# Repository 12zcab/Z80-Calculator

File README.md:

BASED ON PREVIOUS PROJECT [View github Repo](https://github.com/12zcab/Handheld-Z80-Retro-Computer)
# What is this?
This is a portable handheld computer made with z80 customized for assembly language programming and simplified system for educational purpose.
The computer contains a Z80 cpu,a 1602 or 2004 LCD and 2 EEPROM slot,a RAM slot,a buzzer with IO ic driver
Its originally designed for another project and edited for better performance as a programmable calculator.
The circuit is edited to make it more simple.

# What it does?
It's a calculator that you can do programming on!
My final goal is to do complex trigonometry and statistic calculation on this calculator!
Also hopefully I can do a Bad Apple Animation on this device XD

Main Functions:
|Type|Function|
|-|-|
|Varaible|ABCDEHIJKLMNOPQRSTUVWXYZ 26 in total :D Hopefully can support 1*10^-99 to 9.999999999*10^99|
|basic operation|+ - * /|
|Trigo|Sin Cos Tan,ArcSin ArcCos ArcTan|
|Sqrt and indexes|^ NthRoot Sqr Sqrt|
|Log|Ln,Log,e^,10^|
|Formula|Save custom formula to input variables and output the result|
# Why it exists?
I just learnt how computer calculates complicated functions with taylor series simplification and I wanna try it in real life and make my own cool retro calculator :D

# Basic Structure

\##Memory Map

|Address|Compoenent|Function|
|-|-|-|
|0x0000 - 0x7FFF|EEPROM|Executable Code of Operating System|
|0x8000 - 0xFEFF|RAM or EEPROM|Multibanked External EEPROM and RAM|
|0xFF00 - 0xFFFF|IO Outputs|for LCD Buzzer and Keyboard Input Output|
|----|----|----|

# Compoenents
## Main Compoenents

|Name|Usage|Quantity|
|-|-|-|

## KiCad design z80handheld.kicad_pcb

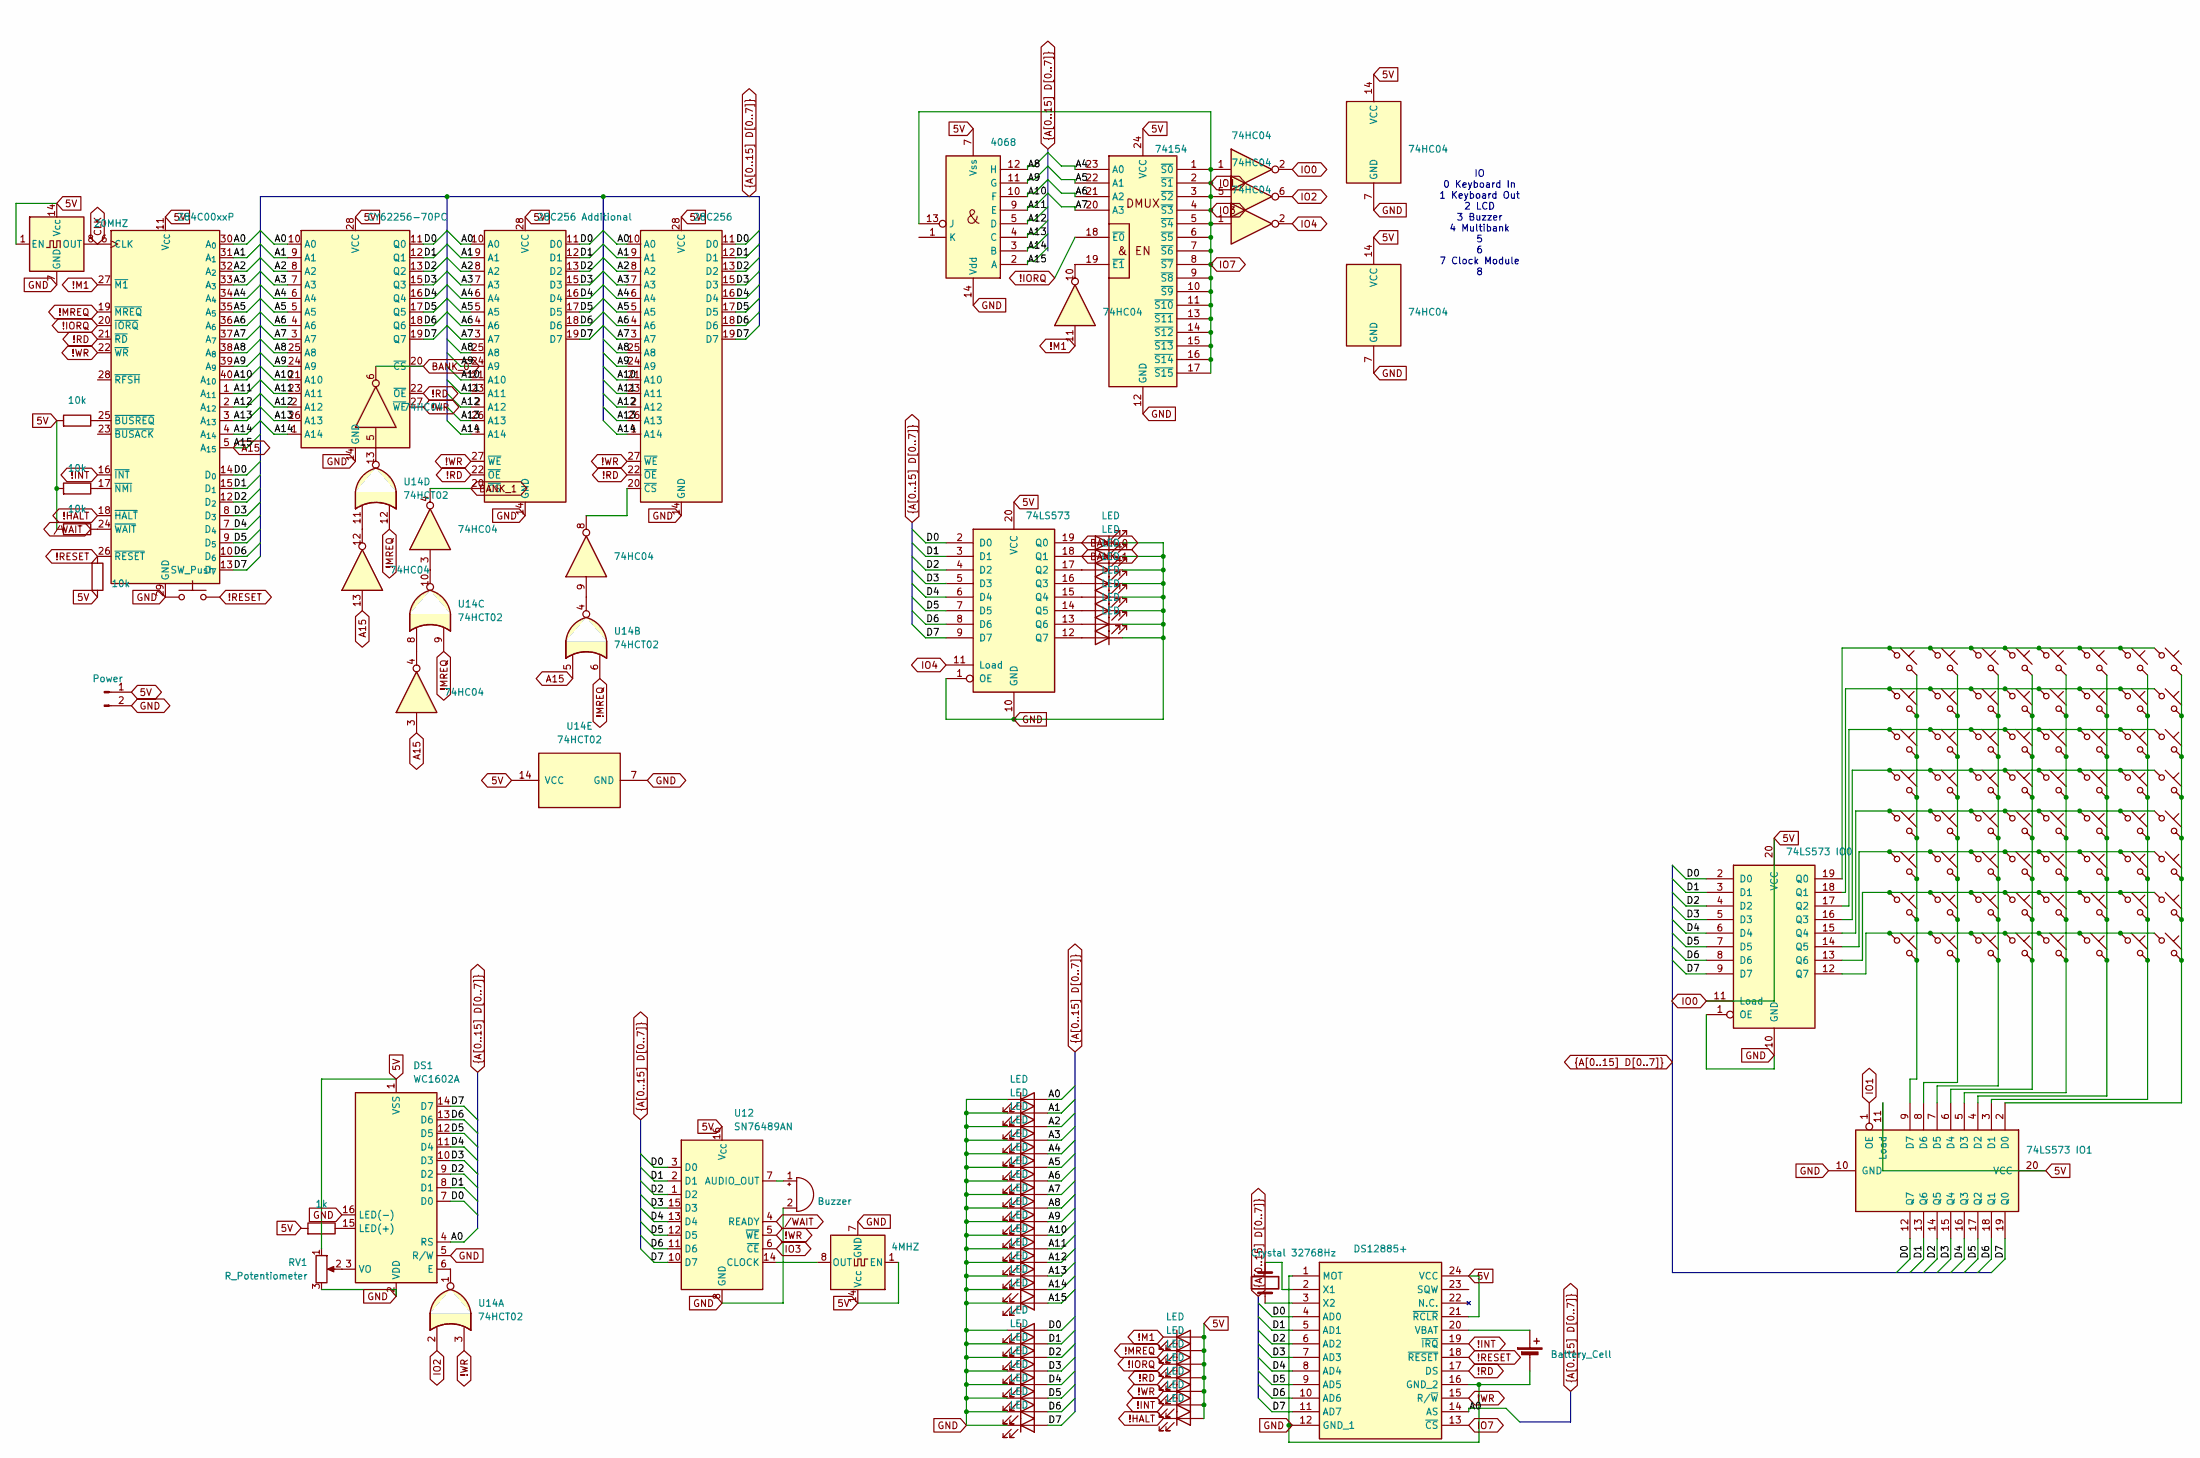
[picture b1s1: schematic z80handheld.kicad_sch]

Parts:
BT1: Battery_Cell; BatteryHolder_MYOUNG_BS-07-A1BJ001_CR2032
BZ1: Buzzer; Buzzer_12x9.5RM7.6
D1, D2, D3, D4, D5, D6, D7, D8, D9, D10, D11, D12, D13, D14, D15, D16, D17, D18, D19, D20, D21, D22, D23, D24, D25, D26, D27, D28, D29, D30, D31, D32, D33, D34, D35, D36, D37, D38, D39: LED; LED_D5.0mm
DS1: WC1602A
IC1: DS12885+; DIP1524W51P254L3175H508Q24N; Manufacturer_Part_Number DS12885+; Mouser Part Number 700-DS12885
J1: Power; PinHeader_1x02_P2.54mm_Vertical
R1, R2, R3, R5: 10k; R_Axial_DIN0207_L6.3mm_D2.5mm_P7.62mm_Horizontal
R4: 1k; R_Axial_DIN0207_L6.3mm_D2.5mm_P7.62mm_Horizontal
RV1: R_Potentiometer; Potentiometer_ACP_CA9-V10_Vertical
SW1, SW2, SW3, SW4, SW5, SW6, SW7, SW8, SW9, SW10, SW11, SW12, SW13, SW14, SW15, SW16, SW17, SW18, SW19, SW20, SW21, SW22, SW23, SW24, SW25, SW26, SW27, SW28, SW29, SW30, SW31, SW32, SW33, SW34, SW35, SW36, SW37, SW38, SW39, SW40, SW41, SW42, SW43, SW44, SW45, SW46, SW47, SW48, SW49, SW50, SW51, SW52, SW53, SW54, SW55, SW56, SW57, SW58, SW59, SW60, SW61, SW62, SW63, SW64: SW_Push_45deg; SW_SPST_PTS810
SW65: SW_Push; SW_PUSH_6mm
U1, U3: 74HC04; DIP-14_W7.62mm
U2: 4068; DIP-14_W7.62mm
U4: 74154; DIP-24_W7.62mm
U5: 74LS573 IO0; DIP-20_W7.62mm
U6: 74LS573; DIP-20_W7.62mm
U7: CY62256-70PC; DIP-28_W15.24mm
U8: 28C256 Additional; DIP-28_W15.24mm
U9: 28C256; DIP-28_W15.24mm
U10: Z84C00xxP; DIP-40_W15.24mm
U11: 74LS573 IO1; DIP-20_W7.62mm
U12: SN76489AN; DIP-16_W7.62mm
U14: 74HCT02; DIP-14_W7.62mm
Y1: 20MHZ; Oscillator_DIP-14
Y2: Crystal 32768Hz; Crystal_C38-LF_D3.0mm_L8.0mm_Vertical
Y3: 4MHZ; Oscillator_DIP-14

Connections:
5V: D6.2 (A), D9.2 (A), D12.2 (A), D15.2 (A), D18.2 (A), D21.2 (A), D24.2 (A), DS1.1 (VSS), IC1.21 (~RCLR), IC1.24 (VCC), J1.1, R1.1, R2.1, R3.1, R5.2, RV1.1, U1.2, U1.14 (VCC), U2.7 (Vss), U3.14 (VCC), U4.24 (VCC), U5.11 (Load), U5.20 (VCC), U6.20 (VCC), U7.28 (VCC), U8.28 (VCC), U9.28 (VCC), U10.11 (V_{CC}), U11.11 (Load), U11.20 (VCC), U12.16 (V_{CC}), U14.14 (VCC), Y1.1 (EN), Y1.14 (Vcc), Y3.1 (EN), Y3.14 (Vcc)
!HALT: D6.1 (K), U10.18 (~HALT)
!INT: D9.1 (K), IC1.19 (~IRQ), U10.16 (~INT)
!IORQ: D18.1 (K), U4.18 (~E0), U10.20 (~IORQ)
!M1: D24.1 (K), U1.11, U10.27 (~M1)
!MREQ: D21.1 (K), U10.19 (~MREQ), U14.6, U14.9, U14.12
!RD: D15.1 (K), IC1.17 (DS), U7.22 (~OE), U8.22 (~OE), U9.22 (~OE), U10.21 (~RD)
!RESET: IC1.18 (~RESET), R5.1, SW65.2, U10.26 (~RESET)
!WR: D12.1 (K), IC1.15 (R/~W), U7.27 (~WE), U8.27 (~WE), U9.27 (~WE), U10.22 (~WR), U12.5 (~WE), U14.3
A0: D1.2 (A), DS1.4 (RS), IC1.14 (AS), U7.10 (A0), U8.10 (A0), U9.10 (A0), U10.30 (A_{0})
A1: D2.2 (A), U7.9 (A1), U8.9 (A1), U9.9 (A1), U10.31 (A_{1})
A2: D4.2 (A), U7.8 (A2), U8.8 (A2), U9.8 (A2), U10.32 (A_{2})
A3: D7.2 (A), U7.7 (A3), U8.7 (A3), U9.7 (A3), U10.33 (A_{3})
A4: D10.2 (A), U4.23 (A0), U7.6 (A4), U8.6 (A4), U9.6 (A4), U10.34 (A_{4})
A5: D13.2 (A), U4.22 (A1), U7.5 (A5), U8.5 (A5), U9.5 (A5), U10.35 (A_{5})
A6: D16.2 (A), U4.21 (A2), U7.4 (A6), U8.4 (A6), U9.4 (A6), U10.36 (A_{6})
A7: D19.2 (A), U4.20 (A3), U7.3 (A7), U8.3 (A7), U9.3 (A7), U10.37 (A_{7})
A8: D22.2 (A), U2.12 (H), U7.25 (A8), U8.25 (A8), U9.25 (A8), U10.38 (A_{8})
A9: D25.2 (A), U2.11 (G), U7.24 (A9), U8.24 (A9), U9.24 (A9), U10.39 (A_{9})
A10: D26.2 (A), U2.10 (F), U7.21 (A10), U8.21 (A10), U9.21 (A10), U10.40 (A_{10})
A11: D27.2 (A), U2.9 (E), U7.23 (A11), U8.23 (A11), U9.23 (A11), U10.1 (A_{11})
A12: D28.2 (A), U2.5 (D), U7.2 (A12), U8.2 (A12), U9.2 (A12), U10.2 (A_{12})
A13: D29.2 (A), U2.4 (C), U7.26 (A13), U8.26 (A13), U9.26 (A13), U10.3 (A_{13})
A14: D30.2 (A), U2.3 (B), U7.1 (A14), U8.1 (A14), U9.1 (A14), U10.4 (A_{14})
A15: D31.2 (A), U1.3, U1.13, U2.2 (A), U10.5 (A_{15}), U14.5
BANK_0: D3.2 (A), U3.6, U6.19 (Q0), U7.20 (~CS)
BANK_1: D5.2 (A), U3.4, U6.18 (Q1), U8.20 (~CS)
CLK: U10.6 (CLK), Y1.8 (OUT)
D0: D32.2 (A), DS1.7 (D0), IC1.4 (AD0), U5.2 (D0), U6.2 (D0), U7.11 (Q0), U8.11 (D0), U9.11 (D0), U10.14 (D_{0}), U11.12 (Q7), U12.3 (D0)
D1: D33.2 (A), DS1.8 (D1), IC1.5 (AD1), U5.3 (D1), U6.3 (D1), U7.12 (Q1), U8.12 (D1), U9.12 (D1), U10.15 (D_{1}), U11.13 (Q6), U12.2 (D1)
D2: D34.2 (A), DS1.9 (D2), IC1.6 (AD2), U5.4 (D2), U6.4 (D2), U7.13 (Q2), U8.13 (D2), U9.13 (D2), U10.12 (D_{2}), U11.14 (Q5), U12.1 (D2)
D3: D35.2 (A), DS1.10 (D3), IC1.7 (AD3), U5.5 (D3), U6.5 (D3), U7.15 (Q3), U8.15 (D3), U9.15 (D3), U10.8 (D_{3}), U11.15 (Q4), U12.15 (D3)
D4: D36.2 (A), DS1.11 (D4), IC1.8 (AD4), U5.6 (D4), U6.6 (D4), U7.16 (Q4), U8.16 (D4), U9.16 (D4), U10.7 (D_{4}), U11.16 (Q3), U12.13 (D4)
D5: D37.2 (A), DS1.12 (D5), IC1.9 (AD5), U5.7 (D5), U6.7 (D5), U7.17 (Q5), U8.17 (D5), U9.17 (D5), U10.9 (D_{5}), U11.17 (Q2), U12.12 (D5)
D6: D38.2 (A), DS1.13 (D6), IC1.10 (AD6), U5.8 (D6), U6.8 (D6), U7.18 (Q6), U8.18 (D6), U9.18 (D6), U10.10 (D_{6}), U11.18 (Q1), U12.11 (D6)
D7: D39.2 (A), DS1.14 (D7), IC1.11 (AD7), U5.9 (D7), U6.9 (D7), U7.19 (Q7), U8.19 (D7), U9.19 (D7), U10.13 (D_{7}), U11.19 (Q0), U12.10 (D7)
GND: BT1.2 (-), BZ1.2 (-), D1.1 (K), D2.1 (K), D3.1 (K), D4.1 (K), D5.1 (K), D7.1 (K), D8.1 (K), D10.1 (K), D11.1 (K), D13.1 (K), D14.1 (K), D16.1 (K), D17.1 (K), D19.1 (K), D20.1 (K), D22.1 (K), D23.1 (K), D25.1 (K), D26.1 (K), D27.1 (K), D28.1 (K), D29.1 (K), D30.1 (K), D31.1 (K), D32.1 (K), D33.1 (K), D34.1 (K), D35.1 (K), D36.1 (K), D37.1 (K), D38.1 (K), D39.1 (K), DS1.2 (VDD), DS1.5 (R/W), DS1.16 (LED(-)), IC1.1 (MOT), IC1.12 (GND_1), IC1.16 (GND_2), J1.2, RV1.3, SW65.1, U1.7 (GND), U2.14 (Vdd), U3.7 (GND), U4.12 (GND), U5.1 (OE), U5.10 (GND), U6.1 (OE), U6.10 (GND), U7.14 (GND), U8.14 (GND), U9.14 (GND), U10.29 (GND), U11.10 (GND), U12.8 (GND), U14.7 (GND), Y1.7 (GND), Y3.7 (GND)
IO1: IC1.13 (~CS), U1.1, U1.5, U2.13 (J), U3.1, U4.1 (~S0), U4.2 (~S1), U4.3 (~S2), U4.4 (~S3), U4.5 (~S4), U4.6 (~S5), U4.7 (~S6), U4.8 (~S7), U4.9 (~S8), U4.10 (~S9), U4.11 (~S10), U4.13 (~S11), U4.14 (~S12), U4.15 (~S13), U4.16 (~S14), U4.17 (~S15), U11.1 (OE), U12.6 (~CE)
IO2: U1.6, U14.2
IO4: U3.2, U6.11 (Load)
unnamed: BT1.1 (+), IC1.20 (VBAT)
unnamed: BZ1.1 (+), U12.7 (AUDIO_OUT)
unnamed: D8.2 (A), U6.17 (Q2)
unnamed: D11.2 (A), U6.16 (Q3)
unnamed: D14.2 (A), U6.15 (Q4)
unnamed: D17.2 (A), U6.14 (Q5)
unnamed: D20.2 (A), U6.13 (Q6)
unnamed: D23.2 (A), U6.12 (Q7)
unnamed: DS1.6 (E), U14.1
unnamed: DS1.15 (LED(+)), R4.2
unnamed: DS1.3 (VO), RV1.2
unnamed: IC1.2 (X1), Y2.2
unnamed: IC1.3 (X2), Y2.1
unnamed: U1.4, U14.8
unnamed: U1.9, U14.4
unnamed: U1.12, U14.11
unnamed: U1.10, U4.19 (~E1)
unnamed: SW1.1, SW2.1, SW3.1, SW4.1, SW5.1, SW6.1, SW7.1, SW8.1, U5.19 (Q0)
unnamed: SW9.1, SW10.1, SW11.1, SW12.1, SW13.1, SW14.1, SW15.1, SW16.1, U5.18 (Q1)
unnamed: SW17.1, SW18.1, SW19.1, SW20.1, SW21.1, SW22.1, SW23.1, SW24.1, U5.17 (Q2)
unnamed: SW25.1, SW26.1, SW27.1, SW28.1, SW29.1, SW30.1, SW31.1, SW32.1, U5.16 (Q3)
unnamed: SW33.1, SW34.1, SW35.1, SW36.1, SW37.1, SW38.1, SW39.1, SW40.1, U5.15 (Q4)
unnamed: SW41.1, SW42.1, SW43.1, SW44.1, SW45.1, SW46.1, SW47.1, SW48.1, U5.14 (Q5)
unnamed: SW49.1, SW50.1, SW51.1, SW52.1, SW53.1, SW54.1, SW55.1, SW56.1, U5.13 (Q6)
unnamed: SW57.1, SW58.1, SW59.1, SW60.1, SW61.1, SW62.1, SW63.1, SW64.1, U5.12 (Q7)
unnamed: U1.8, U9.20 (~CS)
unnamed: R1.2, U10.25 (~BUSREQ)
unnamed: R2.2, U10.17 (~NMI)
unnamed: R3.2, U10.24 (~WAIT)
unnamed: SW8.2, SW16.2, SW24.2, SW32.2, SW40.2, SW48.2, SW56.2, SW64.2, U11.2 (D0)
unnamed: SW7.2, SW15.2, SW23.2, SW31.2, SW39.2, SW47.2, SW55.2, SW63.2, U11.3 (D1)
unnamed: SW6.2, SW14.2, SW22.2, SW30.2, SW38.2, SW46.2, SW54.2, SW62.2, U11.4 (D2)
unnamed: SW5.2, SW13.2, SW21.2, SW29.2, SW37.2, SW45.2, SW53.2, SW61.2, U11.5 (D3)
unnamed: SW4.2, SW12.2, SW20.2, SW28.2, SW36.2, SW44.2, SW52.2, SW60.2, U11.6 (D4)
unnamed: SW3.2, SW11.2, SW19.2, SW27.2, SW35.2, SW43.2, SW51.2, SW59.2, U11.7 (D5)
unnamed: SW2.2, SW10.2, SW18.2, SW26.2, SW34.2, SW42.2, SW50.2, SW58.2, U11.8 (D6)
unnamed: SW1.2, SW9.2, SW17.2, SW25.2, SW33.2, SW41.2, SW49.2, SW57.2, U11.9 (D7)
unnamed: U12.14 (CLOCK), Y3.8 (OUT)
unnamed: U3.3, U14.10
unnamed: U3.5, U14.13
/WAIT: U12.4 (READY)

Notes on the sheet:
IO 0 Keyboard In 1 Keyboard Out 2 LCD 3 Buzzer 4 Multibank 5 6 7 Clock Module 8

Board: 2 copper layers, 131 parts (0 on the bottom side), 80 nets, no tracks yet.
